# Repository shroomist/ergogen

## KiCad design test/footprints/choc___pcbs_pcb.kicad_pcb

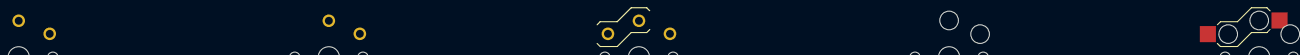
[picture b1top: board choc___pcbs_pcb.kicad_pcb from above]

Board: 2 copper layers, 5 parts (0 on the bottom side), 2 nets, no tracks yet.

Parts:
S1, S2, S3, S4, S5: PG1350

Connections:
from: S1.1, S2.1, S3.1, S4.1, S5.1
to: S1.2, S2.2, S3.2, S4.2, S5.2
